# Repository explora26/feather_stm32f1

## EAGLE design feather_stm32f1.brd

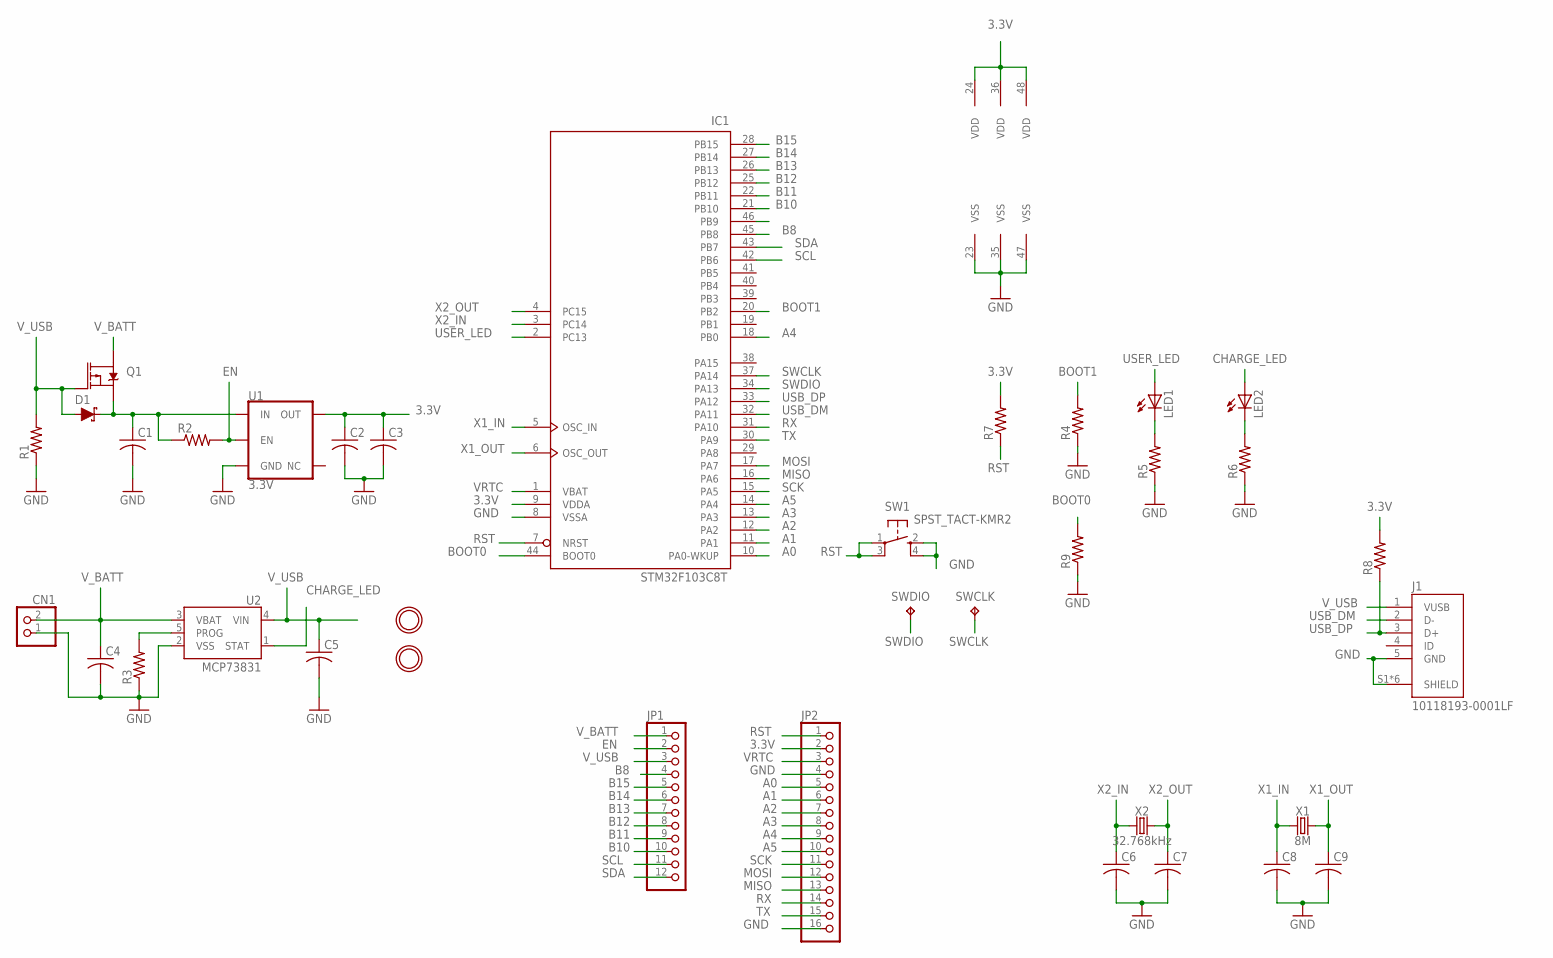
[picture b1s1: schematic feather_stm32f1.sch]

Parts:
C1, C2, C3, C4, C5: C-USC0805; C0805
C6, C7, C8, C9: C-USC0603; C0603
CN1: JST_2PIN-SMT-RA; JST-PH-2-SMT-RA
D1: DIODE-SCHOTTKY-BAT20J; SOD-323
IC1: STM32F103C8T; LQFP48
J1: 10118193-0001LF; FCI_10118193-0001LF
JP1: PINHD-1X12-CB; 1X12-CB
JP2: PINHD16; 1X16-CB
LED1, LED2: LEDCHIPLED_0603; CHIPLED_0603
Q1: MOSFET_PCH-DMG2307L; SOT23-3
R1, R2, R3, R4, R5, R6, R7, R8, R9: R-US_R0603; R0603
SW1: SPST_TACT-KMR2; KMR2
SWCLK: TPTP20R; TP20R
SWDIO: TPTP20R; TP20R
U1: 3.3V; SOT23-5
U2: MCP73831; SOT23-5
U$1, U$31: MOUNTINGHOLE2.5; MOUNTINGHOLE_2.5_PLATED
X1: 8M; CRYSTAL-SMD-5X3.2-2PAD
X2: 32.768kHz; CRYSTAL-SMD-3.2X1.5MM

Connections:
3.3V: C2.1, C3.1, IC1.9 (VDDA), IC1.24 (VDD), IC1.36 (VDD), IC1.48 (VDD), JP2.2, R7.2, R8.2, U1.5 (OUT)
A0: IC1.10 (PA0-WKUP), JP2.5
A1: IC1.11 (PA1), JP2.6
A2: IC1.12 (PA2), JP2.7
A3: IC1.13 (PA3), JP2.8
A4: IC1.18 (PB0), JP2.9
A5: IC1.14 (PA4), JP2.10
B8: IC1.45 (PB8), JP1.4
B10: IC1.21 (PB10), JP1.10
B11: IC1.22 (PB11), JP1.9
B12: IC1.25 (PB12), JP1.8
B13: IC1.26 (PB13), JP1.7
B14: IC1.27 (PB14), JP1.6
B15: IC1.28 (PB15), JP1.5
BOOT0: IC1.44 (BOOT0), R9.2
BOOT1: IC1.20 (PB2), R4.2
CHARGE_LED: LED2.A, U2.1 (STAT)
EN: JP1.2, R2.2, U1.3 (EN)
GND: C1.2, C2.2, C3.2, C4.2, C5.2, C6.2, C7.2, C8.2, C9.2, CN1.1 (2), IC1.8 (VSSA), IC1.23 (VSS), IC1.35 (VSS), IC1.47 (VSS), J1.5 (GND), J1.S1 (SHIELD), J1.S2 (SHIELD), J1.S3 (SHIELD), J1.S4 (SHIELD), J1.S5 (SHIELD), J1.S6 (SHIELD), JP2.4, JP2.16, R1.1, R3.1, R4.1, R5.1, R6.1, R9.1, SW1.2 (S), SW1.4 (S1), U1.2 (GND), U2.2 (VSS)
MISO: IC1.16 (PA6), JP2.13
MOSI: IC1.17 (PA7), JP2.12
unnamed: C1.1, D1.C, Q1.2 (S), R2.1, U1.1 (IN)
unnamed: R3.2, U2.5 (PROG)
unnamed: LED1.C, R5.2
unnamed: LED2.C, R6.2
RST: IC1.7 (NRST), JP2.1, R7.1, SW1.1, SW1.3 (P1)
RX: IC1.31 (PA10), JP2.14
SCK: IC1.15 (PA5), JP2.11
SCL: IC1.42 (PB6), JP1.11
SDA: IC1.43 (PB7), JP1.12
SWCLK: IC1.37 (PA14), SWCLK.TP
SWDIO: IC1.34 (PA13), SWDIO.TP
TX: IC1.30 (PA9), JP2.15
USB_DM: IC1.32 (PA11), J1.2 (D-)
USB_DP: IC1.33 (PA12), J1.3 (D+), R8.1
USER_LED: IC1.2 (PC13), LED1.A
VRTC: IC1.1 (VBAT), JP2.3
V_BATT: C4.1, CN1.2 (1), JP1.1, Q1.3 (D), U2.3 (VBAT)
V_USB: C5.1, D1.A, J1.1 (VUSB), JP1.3, Q1.1 (G), R1.2, U2.4 (VIN)
X1_IN: C8.1, IC1.5 (OSC_IN), X1.P$1 (1)
X1_OUT: C9.1, IC1.6 (OSC_OUT), X1.P$2 (2)
X2_IN: C6.1, IC1.3 (PC14), X2.P$1 (1)
X2_OUT: C7.1, IC1.4 (PC15), X2.P$2 (2)

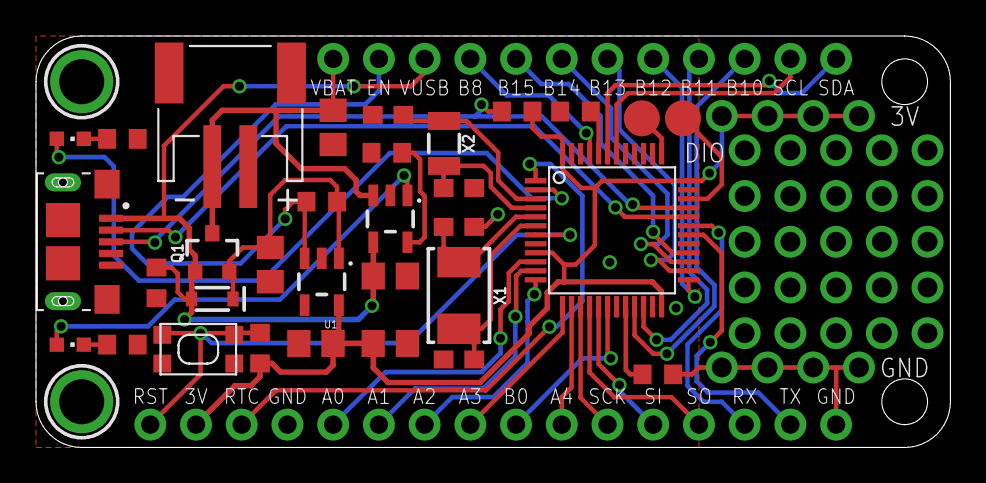
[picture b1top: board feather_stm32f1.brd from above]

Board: 2 copper layers, 50.8 x 22.9 mm, 36 parts (0 on the bottom side), 43 nets.

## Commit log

2019-05-13 Init projcect

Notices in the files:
parts and their libraries:
SparkFun-IC-Power: Licensing: Creative Commons ShareAlike 4.0 International - https://creativecommons.org/licenses/by-sa/4.0
microbuilder: This work is placed in the public domain, and may be freely used for commercial and non-commercial work with the following conditions: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
